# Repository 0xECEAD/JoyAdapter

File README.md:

# JoyAdapter

Another 8-bit Atari Joystick to USB adapter.

There are dozens of similar converters available, but I wanted one in a sleek form factor.
It is about the size of the iconic Atari connector itself. 

It is a standard USB-HID class (Joystick) device, generally no drivers required. It has 2 buttons and 2-axis (non configurable). No POT/Paddle inputs only digital (switch to ground) inputs. 

The LED flashes on connect and movement/button action.

## PCB:

schematic: [pdf](Board/schema.pdf)

### Pinout J1 Atari:
Connector  [Wikipedia](https://en.wikipedia.org/wiki/Atari_joystick_port)

| Pin | Function | Pin | Function |
| ------ | ------ | ------ | ------ |
| 1 | Up | 6 | Button 1 |
| 2 | Down | 7 | +5V |
| 3 | Left | 8 | Ground |
| 4 | Right | 9 | Button 2 |
| 5 | N.C. |

**Note:** +5V on pin 7 (not fused or limitied or protected) can damage you USB host if shorted.
5V is not required for most (passive) joysticks i know, so you could pull pin 7 the out of the connector to be safe.

### Parts: 

|Qty|Ref(s)|Value|Manufacturer|Note|Datasheet|
| ------ | ------ | ------ | ------ | ------ | ------ |
|1|C1|4u7F||Tantalum||
|1|C2|1uF||||
|1|C3|100nF||||
|1|D1|L-424IDT|Kingbright|FlatTop|[pdf](https://nl.mouser.com/datasheet/2/216/L-424IDT(Ver.12A)-795377.pdf)|
|1|H1|MountingHole||2.5mm||
|1|J1|DB9 Male||Solder Straight, shell removed||
|1|J3|USB PLUG Type A|Keystone Electronics|SMD|[pdf](https://www.mouser.com/datasheet/2/215/31-744008.pdf)|
|2|J4, J5|Connector 1x2||pitch 1.27mm||
|1|R1|68Ω||||
|1|U1|XC6220B331MR|Torex Semiconductor||[pdf](https://www.torexsemi.com/file/xc6220/XC6220.pdf)|
|1|U2|STM32F042G6Ux|STMicroelectronics|QFN28 4x4mm|[pdf](http://www.st.com/st-web-ui/static/active/en/resource/technical/document/datasheet/DM00105814.pdf)|

Notes: 
- The J1 shell is actually a **DE**-type (common mistake, even KiCad fails this)
- Any low-drop voltage regulator for U1 (SOT23-5 package) either 3V or 3V3, e.q. XC6220B331MR or AP7383-30W5.
- U2 is a STM32F042G6Ux controller, it features crystal-less USB, and 5V tolerant inputs.
- The SWD programming connector was split into two, J4 and J5 due to size restrictions.

### Construction:

Manufacture the PCB with FR4 thickness 1.2mm. (Normal 1.6mm will not fit between the pins of J1).

J1 is a standard DSUB 9pin Male connector. Remove the shell with cutters and pliers and some force.
The remaining inner part can be mounted with the PCB between the pins. 

Solder the LED so the flat top aligns nicely with the top side of the case.

## Case:

Print the Bottom and Top part of the case on your 3D printer (i used a Ultimaker S5).
Use a M2.5 x 8mm Hex Socket Head Cap Screw to join bottom case and top case together.

## Software:

Project setup was done with [STM CubeMX](https://www.st.com/en/development-tools/stm32cubemx.html), further implementation with [VisualGDB](https://visualgdb.com/).
The [Descriptor Tool](https://www.usb.org/document-library/hid-descriptor-tool) was used to design the HID Report.
Its a fairly simple source code, you can adjust it to you favorite development environment.

### Latency:

Updates 100x per second, reason mostly to reduce contact bounce. 
In theory you could send at 1kHz for LowSpeed USB or 8kHz for FullSpeed USB, but you may want to include some debounce logic.
Current implementation thus updates every change in a 10ms interval, faster then most screen refresh rates of retro games. 

## Compatibility
Windows 98/XP/Vista/7/8/10/11, Mac OSX, Linux, RaspberryPI, MiSTer. 

### Tested Devices
The Arcade by S.T.C. Rotterdam

### Design Software

KiCad v6.0.7 + GerberView v2.6.1
FreeCAD v0.19
Ultimaker Cura v4.6.2

Descriptor Tool, Version 2.4
VisualGDB v5.6r8 + STM CubeMX v6.5

### Demo

## Credits
(c) 2019 Enceladus

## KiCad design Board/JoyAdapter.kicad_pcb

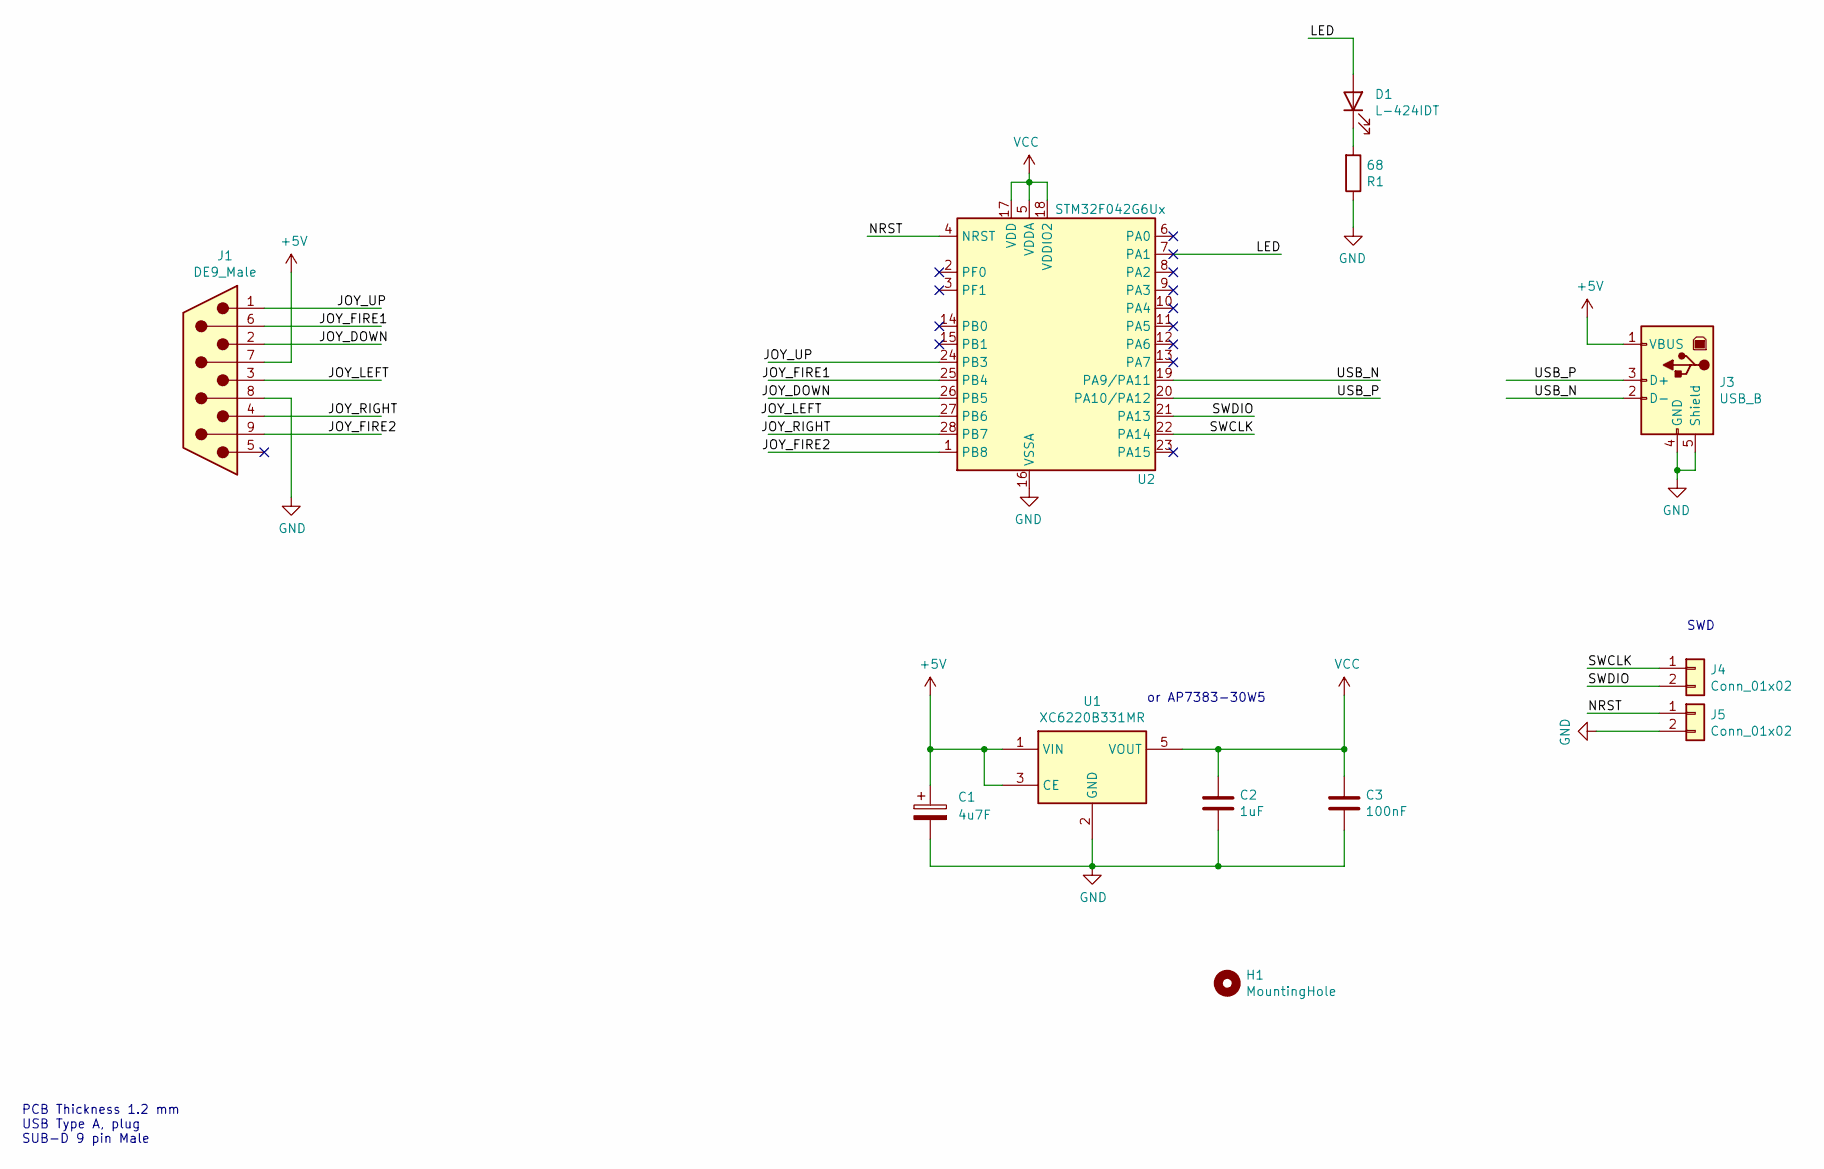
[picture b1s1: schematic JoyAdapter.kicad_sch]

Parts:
C1: 4u7F
C2: 1uF; C_0805_2012Metric_Pad1.15x1.40mm_HandSolder
C3: 100nF; C_0805_2012Metric_Pad1.15x1.40mm_HandSolder
D1: L-424IDT; LED_D3.0mm_FlatTop
H1: MountingHole; MountingHole_2.5mm
J1: DE9_Male; DSUB-9_Male_EdgeMount_P2.77mm
J3: USB_B; USB_A_Lumberg_2410-08
J4, J5: Conn_01x02; PinHeader_1x02_P1.27mm_Vertical
R1: 68; R_0805_2012Metric_Pad1.15x1.40mm_HandSolder
U1: XC6220B331MR; SOT-23-5
U2: STM32F042G6Ux; QFN-28_4x4mm_P0.5mm

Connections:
+5V: C1.1, J1.7, J3.1 (VBUS), U1.1 (VIN), U1.3 (CE)
/JOY_DOWN: J1.2, U2.26 (PB5)
/JOY_FIRE1: J1.6, U2.25 (PB4)
/JOY_FIRE2: J1.9, U2.1 (PB8)
/JOY_LEFT: J1.3, U2.27 (PB6)
/JOY_RIGHT: J1.4, U2.28 (PB7)
/JOY_UP: J1.1, U2.24 (PB3)
/LED: D1.2 (A), U2.7 (PA1)
/NRST: J5.1, U2.4 (NRST)
/SWCLK: J4.1, U2.22 (PA14)
/SWDIO: J4.2, U2.21 (PA13)
/USB_N: J3.2 (D-), U2.19 (PA9/PA11)
/USB_P: J3.3 (D+), U2.20 (PA10/PA12)
GND: C1.2, C2.2, C3.2, J1.8, J3.4 (GND), J3.5 (Shield), J5.2, R1.1, U1.2 (GND), U2.16 (VSSA)
unnamed: D1.1 (K), R1.2
VCC: C2.1, C3.1, U1.5 (VOUT), U2.5 (VDDA), U2.17 (VDD), U2.18 (VDDIO2)

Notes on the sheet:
or AP7383-30W5
SWD
PCB Thickness 1.2 mm USB Type A, plug SUB-D 9 pin Male

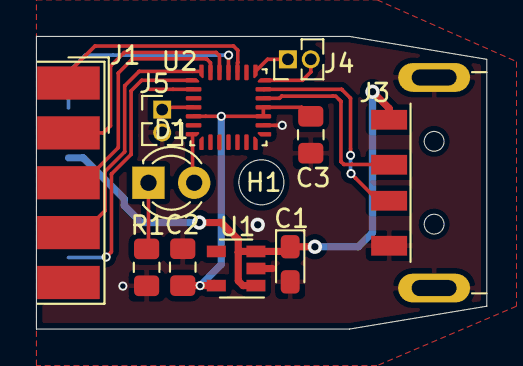
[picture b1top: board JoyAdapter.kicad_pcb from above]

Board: 2 copper layers, 25.0 x 16.3 mm, 12 parts (0 on the bottom side), 16 nets.

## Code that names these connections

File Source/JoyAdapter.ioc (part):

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Mcu.Name=STM32F042G(4-6)Ux
Mcu.Package=UFQFPN28
Mcu.UserName=STM32F042G6Ux
PA1.Signal=S_TIM2_CH2
PA11.Mode=Device
PA11.Signal=USB_DM
PA12.Mode=Device
PA12.Signal=USB_DP
PA13.Mode=Serial_Wire
PA13.Signal=SYS_SWDIO
PA14.Mode=Serial_Wire
PA14.Signal=SYS_SWCLK
PB3.GPIOParameters=GPIO_PuPd,GPIO_Label
PB3.GPIO_Label=JOY_UP
PB3.GPIO_PuPd=GPIO_PULLUP
PB3.Signal=GPIO_Input
PB4.GPIOParameters=GPIO_PuPd,GPIO_Label
PB4.GPIO_Label=JOY_FIRE1
PB4.GPIO_PuPd=GPIO_PULLUP
PB4.Signal=GPIO_Input
PB5.GPIOParameters=GPIO_PuPd,GPIO_Label
PB5.GPIO_Label=JOY_DOWN
PB5.GPIO_PuPd=GPIO_PULLUP
PB5.Signal=GPIO_Input
PB6.GPIOParameters=GPIO_PuPd,GPIO_Label
PB6.GPIO_Label=JOY_LEFT
PB6.GPIO_PuPd=GPIO_PULLUP
PB6.Signal=GPIO_Input
PB7.GPIOParameters=GPIO_PuPd,GPIO_Label
PB7.GPIO_Label=JOY_RIGHT
PB7.GPIO_PuPd=GPIO_PULLUP
PB7.Signal=GPIO_Input
PB8.GPIOParameters=GPIO_PuPd,GPIO_Label
PB8.GPIO_Label=JOY_FIRE2
PB8.GPIO_PuPd=GPIO_PULLUP
PB8.Signal=GPIO_Input
RCC.SYSCLKFreq_VALUE=48000000
RCC.SYSCLKSource=RCC_SYSCLKSOURCE_HSI48
board=custom

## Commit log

2022-10-23 Initial
